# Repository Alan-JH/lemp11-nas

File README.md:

# lemp11-nas
Lemur Pro 11 to Low Power NAS Conversion

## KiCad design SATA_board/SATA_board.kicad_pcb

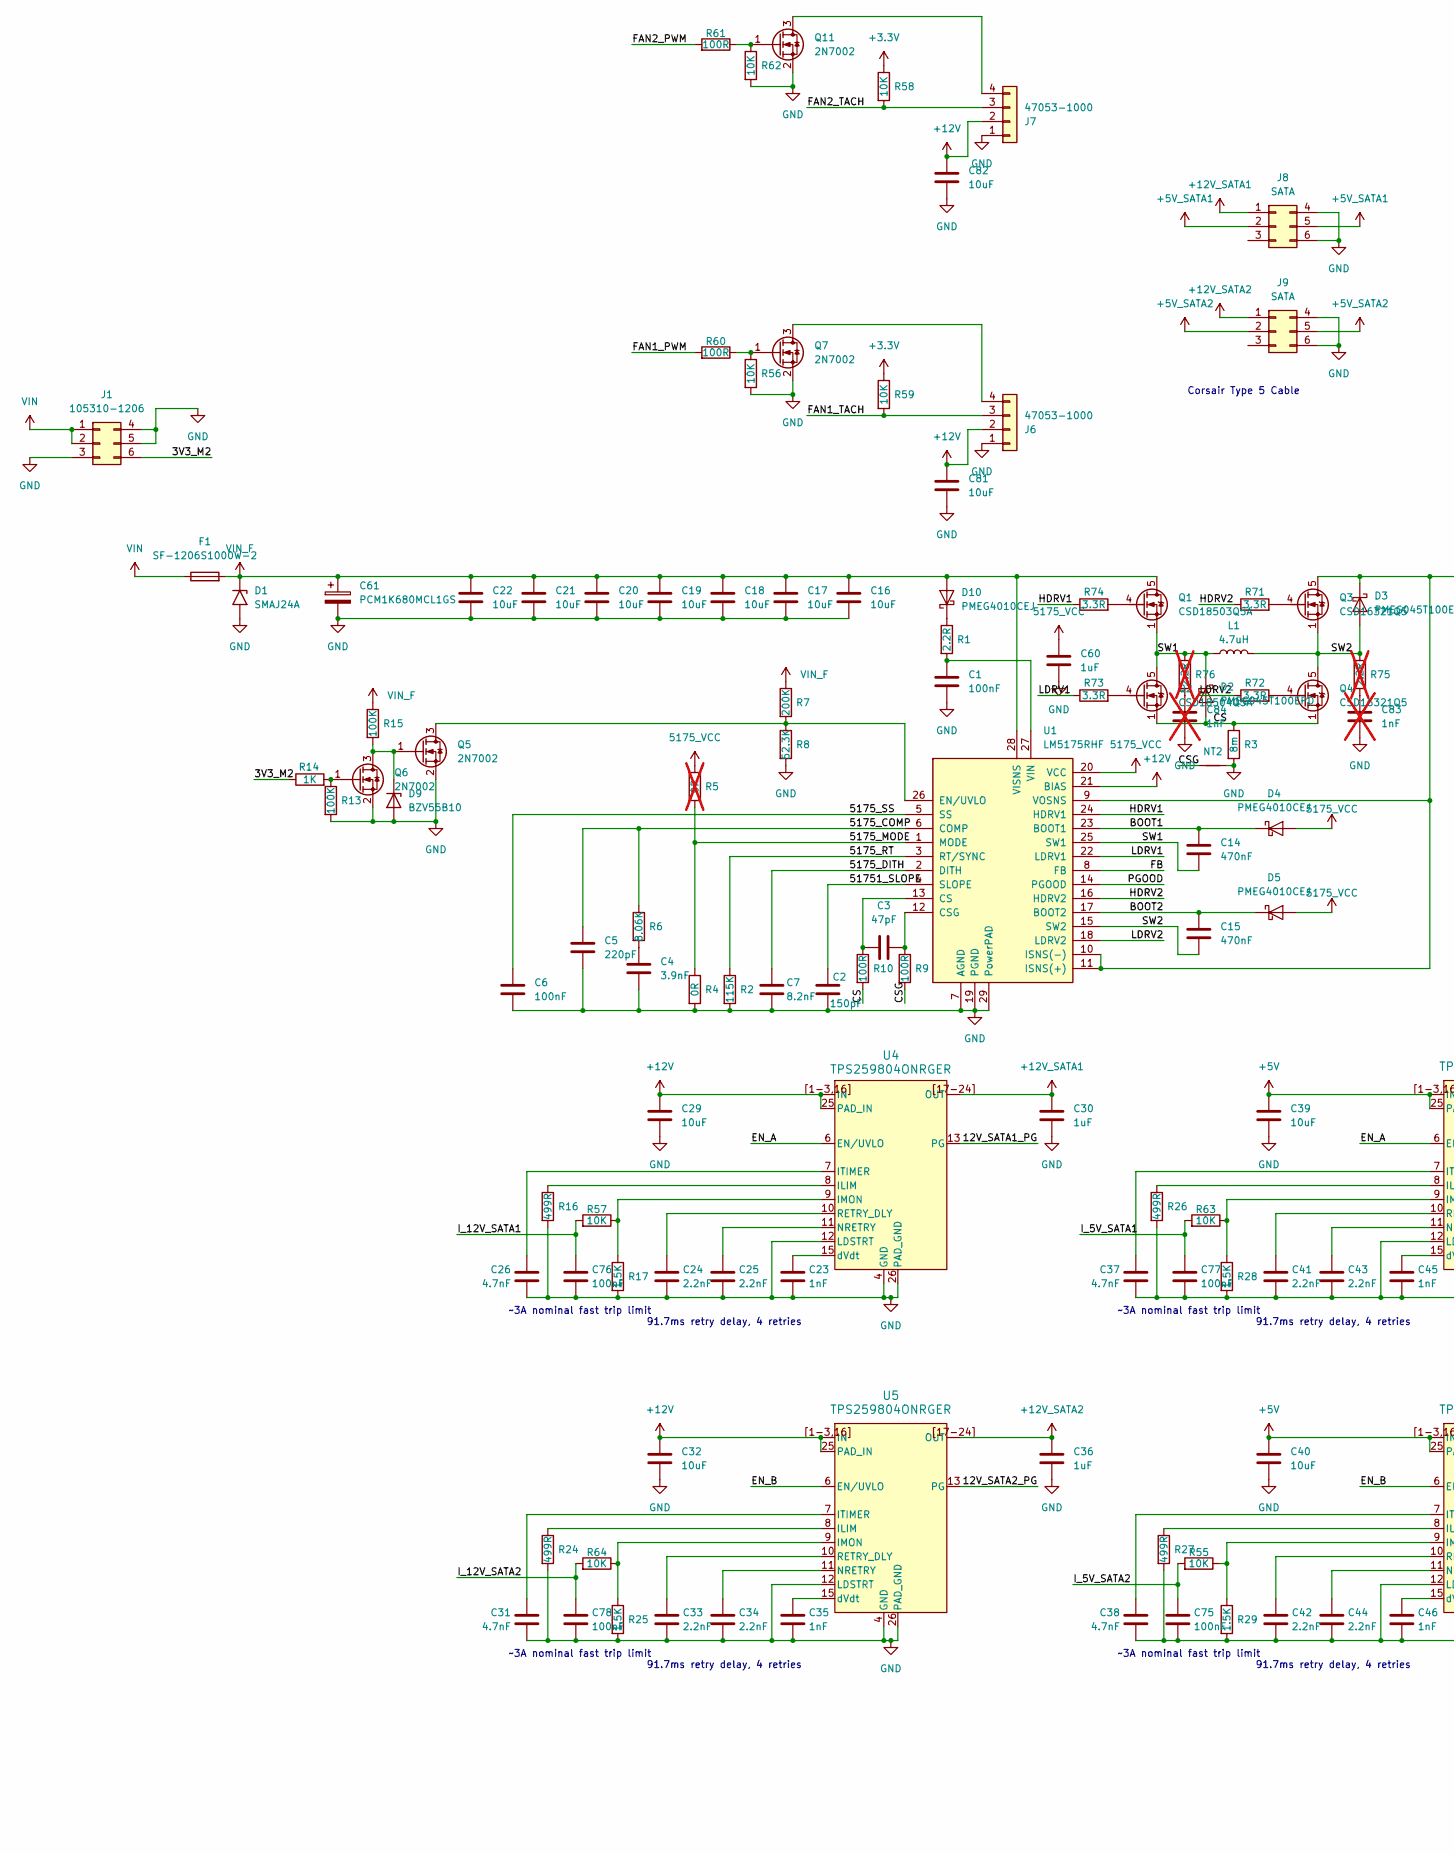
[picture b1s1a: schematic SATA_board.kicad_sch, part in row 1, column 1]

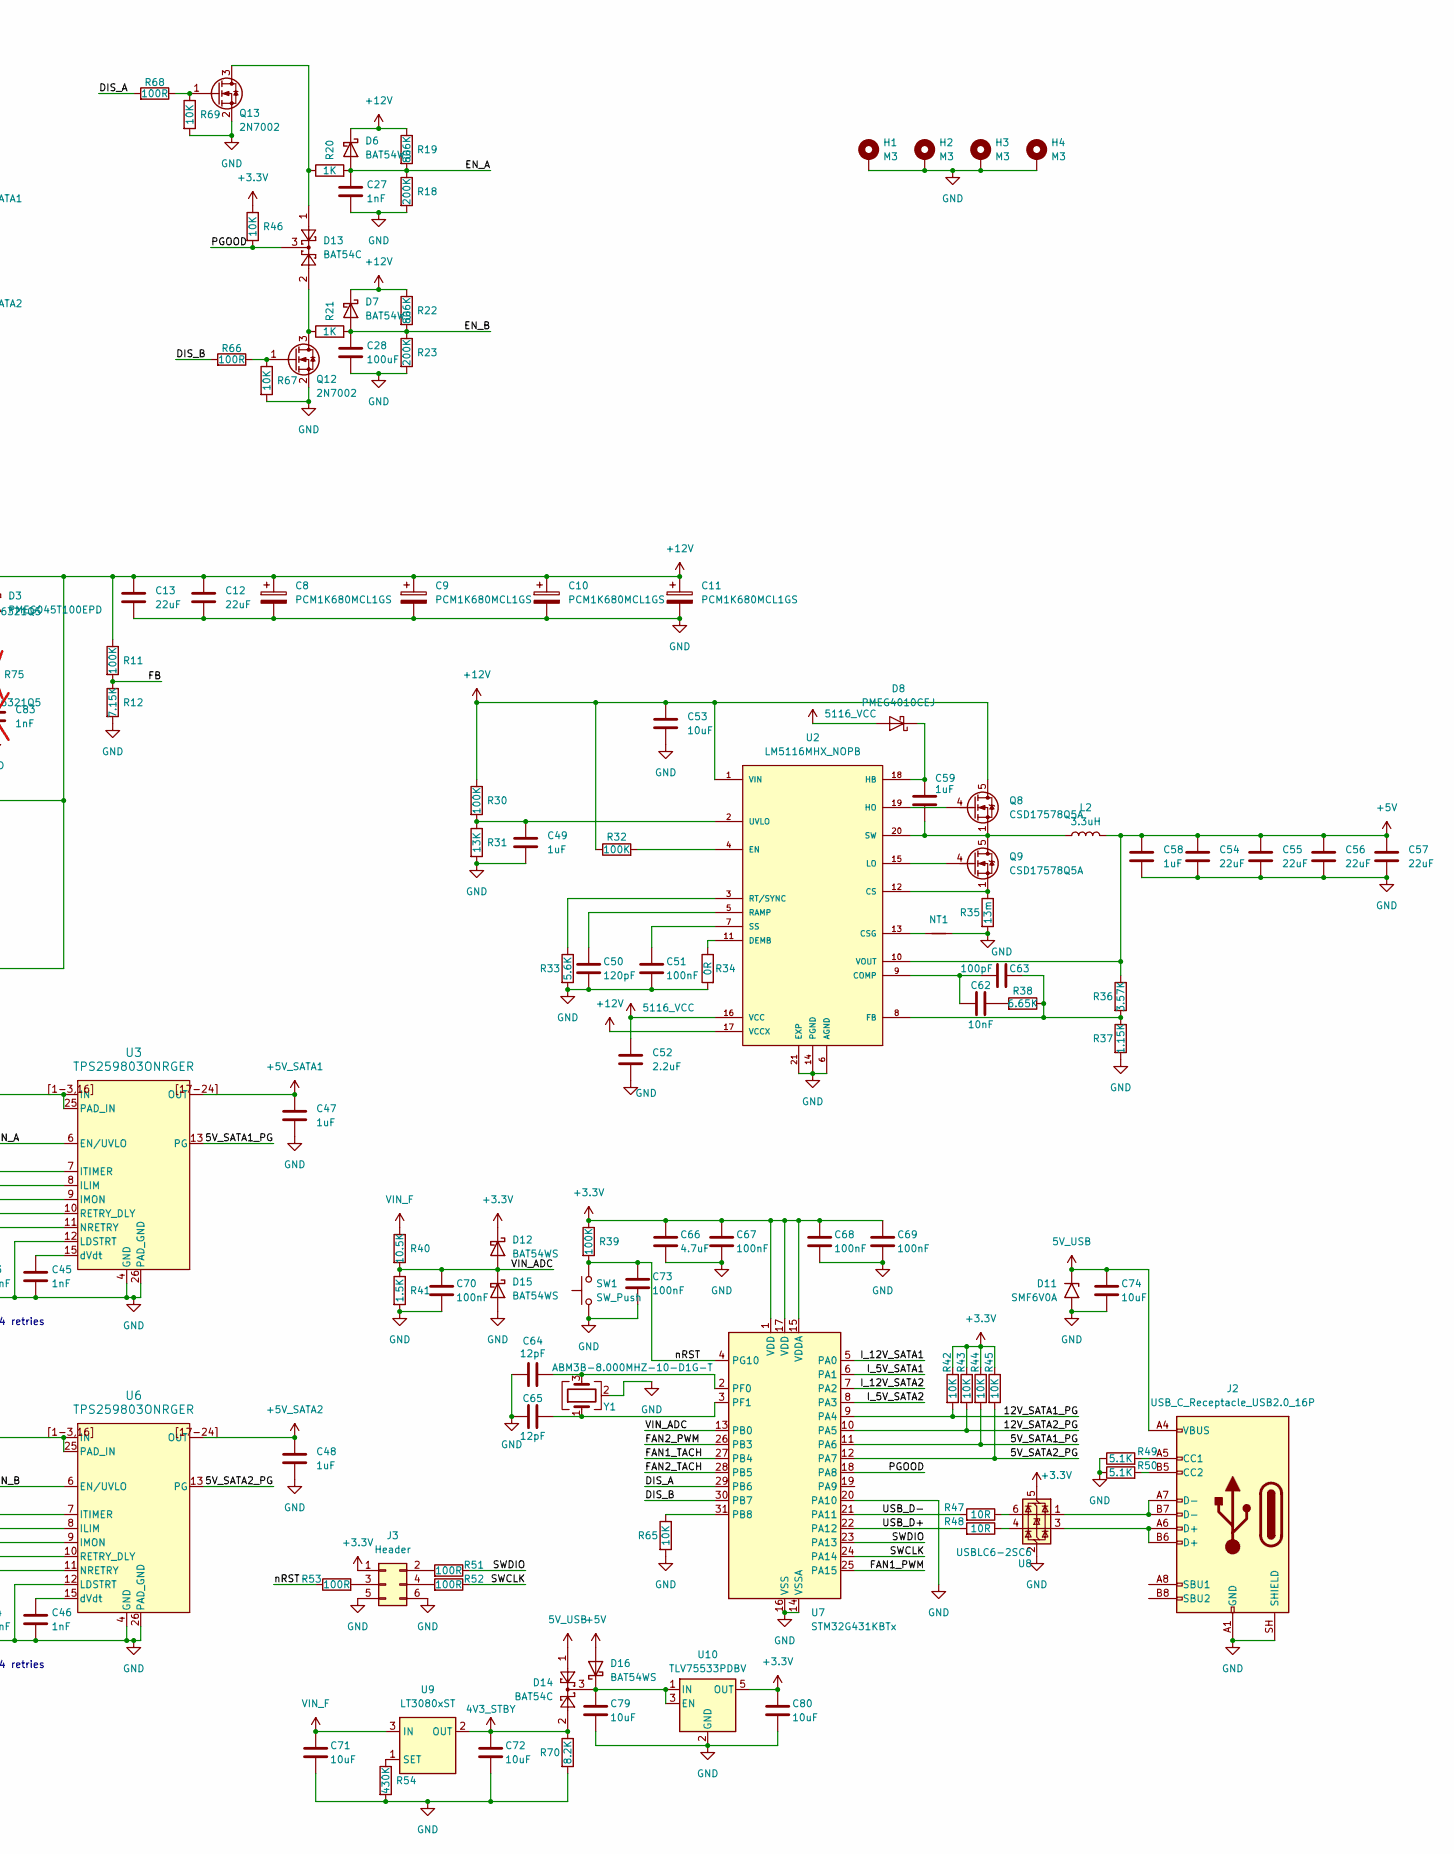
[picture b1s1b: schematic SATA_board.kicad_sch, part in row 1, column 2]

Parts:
C1, C51, C67, C68, C69, C70, C73, C75, C76, C77, C78: 100nF; C_0603_1608Metric
C2: 150pF; C_0402_1005Metric
C3: 47pF; C_0402_1005Metric
C4: 3.9nF; C_0402_1005Metric
C5: 220pF; C_0402_1005Metric
C6: 100nF; C_0402_1005Metric
C7: 8.2nF; C_0402_1005Metric
C8, C9, C10, C11, C61: PCM1K680MCL1GS; CP_Elec_10x10
C12, C13, C54, C55, C56, C57: 22uF; C_1210_3225Metric
C14, C15: 470nF; C_0603_1608Metric
C16, C17, C18, C19, C20, C21, C22, C53, C71: 10uF; C_1210_3225Metric
C23, C27, C35, C45, C46: 1nF; C_0603_1608Metric
C24, C25, C33, C34, C41, C42, C43, C44: 2.2nF; C_0603_1608Metric
C26, C31, C37, C38: 4.7nF; C_0603_1608Metric
C28: 100uF; C_1210_3225Metric
C29, C32, C39, C40, C72, C74, C79, C80, C81, C82: 10uF; C_0805_2012Metric
C30, C36, C47, C48, C49, C58, C59, C60: 1uF; C_0603_1608Metric
C50: 120pF; C_0603_1608Metric
C52: 2.2uF; C_0603_1608Metric
C62: 10nF; C_0603_1608Metric
C63: 100pF; C_0603_1608Metric
C64, C65: 12pF; C_0402_1005Metric
C66: 4.7uF; C_0603_1608Metric
C83, C84: 1nF; C_0805_2012Metric; not fitted
D1: SMAJ24A; D_SMA
D2, D3: PMEG045T100EPD; Nexperia_CFP15_SOT-1289
D4, D5, D8, D10: PMEG4010CEJ; D_SOD-323F
D6, D7, D12, D15, D16: BAT54WS; D_SOD-323F
D9: BZV55B10; D_MiniMELF
D11: SMF6V0A; D_SMF
D13, D14: BAT54C; SOT-23
F1: SF-1206S1000W-2; Fuse_1206_3216Metric
H1, H2, H3, H4: M3; MountingHole_3.2mm_M3_DIN965_Pad
J1: 105310-1206; Molex_Nano-Fit_105310-xx06_2x03_P2.50mm_Vertical
J2: USB_C_Receptacle_USB2.0_16P; USB_C_Receptacle_GCT_USB4105-xx-A_16P_TopMnt_Horizontal
J3: Header; PinHeader_2x03_P2.54mm_Vertical
J6, J7: 47053-1000; FanPinHeader_1x04_P2.54mm_Vertical
J8, J9: SATA; Molex_Micro-Fit_3.0_43045-0612_2x03_P3.00mm_Vertical
L1: 4.7uH; L_Vishay_IHLP-6767
L2: 3.3uH; L_Vishay_IHLP-4040
NT1, NT2: NetTie-2_SMD_Pad0.5mm
Q1: CSD18503Q5A; TDSON-8-1
Q2: CSD18504Q5A; TDSON-8-1
Q3, Q4: CSD16321Q5; TDSON-8-1
Q5, Q6, Q7, Q11, Q12, Q13: 2N7002; SOT-23
Q8, Q9: CSD17578Q5A; TDSON-8-1
R1: 2.2R; R_0603_1608Metric
R2: 115K; R_0402_1005Metric
R3: 8m; R_2512_6332Metric
R4: 0R; R_0402_1005Metric
R5: 0R; R_0402_1005Metric; not fitted
R6: 8.06K; R_0402_1005Metric
R7, R18, R23: 200K; R_0603_1608Metric
R8: 52.3K; R_0603_1608Metric
R9, R10: 100R; R_0402_1005Metric
R11, R13, R15, R30, R32, R39: 100K; R_0603_1608Metric
R12: 7.15K; R_0603_1608Metric
R14, R20, R21: 1K; R_0603_1608Metric
R16, R24, R26, R27: 499R; R_0603_1608Metric
R17, R25, R28, R29, R41: 1.5K; R_0603_1608Metric
R19, R22: 806K; R_0603_1608Metric
R31: 13K; R_0603_1608Metric
R33: 5.6K; R_0603_1608Metric
R34: 0R; R_0603_1608Metric
R35: 13m; R_2512_6332Metric
R36: 3.57K; R_0603_1608Metric
R37: 1.15K; R_0603_1608Metric
R38: 6.65K; R_0603_1608Metric
R40: 10.5K; R_0603_1608Metric
R42, R43, R44, R45, R46, R55, R56, R57, R58, R59, R62, R63, R64, R65, R67, R69: 10K; R_0603_1608Metric
R47, R48: 10R; R_0402_1005Metric
R49, R50: 5.1K; R_0402_1005Metric
R51, R52, R53, R60, R61, R66, R68: 100R; R_0603_1608Metric
R54: 430K; R_0603_1608Metric
R70: 8.2K; R_0603_1608Metric
R71, R72, R73, R74: 3.3R; R_0402_1005Metric
R75, R76: 2.2R; R_0805_2012Metric; not fitted
SW1: SW_Push; SW_PUSH_6mm
U1: LM5175RHF; VQFN-28-1EP_4x5mm_P0.5mm_EP2.55x3.55mm
U2: LM5116MHX_NOPB; SOP65P640X110-21N; PARTREV H
U3, U6: TPS259803ONRGER; IC24_TPS259802ONRGER_TEX
U4, U5: TPS259804ONRGER; IC24_TPS259802ONRGER_TEX
U7: STM32G431KBTx; LQFP-32_7x7mm_P0.8mm
U8: USBLC6-2SC6; SOT-23-6
U9: LT3080xST; SOT-223
U10: TLV75533PDBV; SOT-23-5
Y1: ABM3B-8.000MHZ-10-D1G-T; Crystal_SMD_Abracon_ABM3B-4Pin_5.0x3.2mm

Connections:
4V3_STBY: C72.1, D14.2, R70.1, U9.2 (OUT), U9.4 (OUT)
5V_USB: C74.1, D11.1 (A1), D14.1, J2.A4 (VBUS), J2.A9 (VBUS), J2.B4 (VBUS), J2.B9 (VBUS)
5116_VCC: C52.1, D8.2 (A), U2.16 (VCC)
5175_VCC: C60.1, D4.2 (A), D5.2 (A), R5.1, U1.20 (VCC)
+3.3V: C66.1, C67.1, C68.1, C69.1, C80.1, D12.1 (K), J3.1, R39.1, R42.1, R43.1, R44.1, R45.1, R46.1, R58.1, R59.1, U7.1 (VDD), U7.15 (VDDA), U7.17 (VDD), U8.5 (VBUS), U10.5 (OUT)
+5V: C39.1, C40.1, C54.1, C55.1, C56.1, C57.1, C58.1, D16.2 (A), L2.2, R36.1, U2.10 (VOUT), U3.1 (IN), U3.2 (IN), U3.3 (IN), U3.16 (IN), U3.25 (PAD_IN), U3.[1-3,16] (IN), U6.1 (IN), U6.2 (IN), U6.3 (IN), U6.16 (IN), U6.25 (PAD_IN), U6.[1-3,16] (IN)
+5V_SATA1: C47.1, J8.2, J8.5, U3.17 (OUT), U3.18 (OUT), U3.19 (OUT), U3.20 (OUT), U3.21 (OUT), U3.22 (OUT), U3.23 (OUT), U3.24 (OUT), U3.[17-24] (OUT)
+5V_SATA2: C48.1, J9.2, J9.5, U6.17 (OUT), U6.18 (OUT), U6.19 (OUT), U6.20 (OUT), U6.21 (OUT), U6.22 (OUT), U6.23 (OUT), U6.24 (OUT), U6.[17-24] (OUT)
+12V: C8.1, C9.1, C10.1, C11.1, C12.1, C13.1, C29.1, C32.1, C53.1, C81.1, C82.1, D3.3 (K), D6.1 (K), D7.1 (K), J6.2, J7.2, Q3.5 (D), Q8.5 (D), R11.1, R19.1, R22.1, R30.1, R32.1, U1.9 (VOSNS), U1.10 (ISNS(-)), U1.11 (ISNS(+)), U1.21 (BIAS), U2.1 (VIN), U2.17 (VCCX), U4.1 (IN), U4.2 (IN), U4.3 (IN), U4.16 (IN), U4.25 (PAD_IN), U4.[1-3,16] (IN), U5.1 (IN), U5.2 (IN), U5.3 (IN), U5.16 (IN), U5.25 (PAD_IN), U5.[1-3,16] (IN)
+12V_SATA1: C30.1, J8.1, U4.17 (OUT), U4.18 (OUT), U4.19 (OUT), U4.20 (OUT), U4.21 (OUT), U4.22 (OUT), U4.23 (OUT), U4.24 (OUT), U4.[17-24] (OUT)
+12V_SATA2: C36.1, J9.1, U5.17 (OUT), U5.18 (OUT), U5.19 (OUT), U5.20 (OUT), U5.21 (OUT), U5.22 (OUT), U5.23 (OUT), U5.24 (OUT), U5.[17-24] (OUT)
/3V3_M2: J1.6, R14.1
/5V_SATA1_PG: R44.2, U3.13 (PG), U7.11 (PA6)
/5V_SATA2_PG: R45.2, U6.13 (PG), U7.12 (PA7)
/12V_SATA1_PG: R42.2, U4.13 (PG), U7.9 (PA4)
/12V_SATA2_PG: R43.2, U5.13 (PG), U7.10 (PA5)
/5175_COMP: C5.1, R6.1, U1.6 (COMP)
/5175_DITH: C7.1, U1.2 (DITH)
/5175_MODE: R4.1, R5.2, U1.1 (MODE)
/5175_RT: R2.1, U1.3 (RT/SYNC)
/5175_SS: C6.1, U1.5 (SS)
/51751_SLOPE: C2.1, U1.4 (SLOPE)
/BOOT1: C14.1, D4.1 (K), U1.23 (BOOT1)
/BOOT2: C15.1, D5.1 (K), U1.17 (BOOT2)
/CS: D2.1 (A), D2.2 (A), Q2.1 (S), Q2.2 (S), Q2.3 (S), Q4.1 (S), Q4.2 (S), Q4.3 (S), R3.1, R10.2
/CSG: NT2.1, R9.2
/DIS_A: R68.2, U7.29 (PB6)
/DIS_B: R66.2, U7.30 (PB7)
/EN_A: C27.1, D6.2 (A), R18.1, R19.2, R20.2, U3.6 (EN/UVLO), U4.6 (EN/UVLO)
/EN_B: C28.1, D7.2 (A), R21.2, R22.2, R23.1, U5.6 (EN/UVLO), U6.6 (EN/UVLO)
/FAN1_PWM: R60.2, U7.25 (PA15)
/FAN1_TACH: J6.3, R59.2, U7.27 (PB4)
/FAN2_PWM: R61.2, U7.26 (PB3)
/FAN2_TACH: J7.3, R58.2, U7.28 (PB5)
/FB: R11.2, R12.1, U1.8 (FB)
/HDRV1: R74.1, U1.24 (HDRV1)
/HDRV2: R71.1, U1.16 (HDRV2)
/I_5V_SATA1: C77.1, R63.2, U7.6 (PA1)
/I_5V_SATA2: C75.1, R55.2, U7.8 (PA3)
/I_12V_SATA1: C76.1, R57.2, U7.5 (PA0)
/I_12V_SATA2: C78.1, R64.2, U7.7 (PA2)
/LDRV1: R73.1, U1.22 (LDRV1)
/LDRV2: R72.1, U1.18 (LDRV2)
/PGOOD: D13.3, R46.2, U1.14 (PGOOD), U7.18 (PA8)
/SW1: C14.2, D2.3 (K), L1.1, Q1.1 (S), Q1.2 (S), Q1.3 (S), Q2.5 (D), R76.1, U1.25 (SW1)
/SW2: C15.2, D3.1 (A), D3.2 (A), L1.2, Q3.1 (S), Q3.2 (S), Q3.3 (S), Q4.5 (D), R75.1, U1.15 (SW2)
/SWCLK: R52.1, U7.24 (PA14)
/SWDIO: R51.1, U7.23 (PA13)
/USB_D+: R48.2, U7.22 (PA12)
/USB_D-: R47.2, U7.21 (PA11)
/VIN_ADC: C70.1, D12.2 (A), D15.1 (K), R40.2, R41.1, U7.13 (PB0)
/nRST: C73.1, R39.2, R53.1, SW1.2, U7.4 (PG10)
GND: C1.2, C2.2, C4.2, C5.2, C6.2, C7.2, C8.2, C9.2, C10.2, C11.2, C12.2, C13.2, C16.2, C17.2, C18.2, C19.2, C20.2, C21.2, C22.2, C23.2, C24.2, C25.2, C26.2, C27.2, C28.2, C29.2, C30.2, C31.2, C32.2, C33.2, C34.2, C35.2, C36.2, C37.2, C38.2, C39.2, C40.2, C41.2, C42.2, C43.2, C44.2, C45.2, C46.2, C47.2, C48.2, C49.2, C50.2, C51.2, C52.2, C53.2, C54.2, C55.2, C56.2, C57.2, C58.2, C60.2, C61.2, C64.1, C65.1, C66.2, C67.2, C68.2, C69.2, C70.2, C71.2, C72.2, C73.2, C74.2, C75.2, C76.2, C77.2, C78.2, C79.2, C80.2, C81.2, C82.2, C83.2, C84.2, D1.2 (A2), D9.2 (A), D11.2 (A2), D15.2 (A), H1.1 (1_1), H2.1 (1_1), H3.1 (1_1), H4.1 (1_1), J1.3, J1.4, J1.5, J2.A1 (GND), J2.A12 (GND), J2.B1 (GND), J2.B12 (GND), J2.SH (SHIELD), J3.5, J3.6, J6.1, J7.1, J8.4, J8.6, J9.4, J9.6, NT1.2, NT2.2, Q5.2 (S), Q6.2 (S), Q7.2 (S), Q11.2 (S), Q12.2 (S), Q13.2 (S), R2.2, R3.2, R4.2, R8.2, R12.2, R13.2, R16.2, R17.2, R18.2, R23.2, R24.2, R25.2, R26.2, R27.2, R28.2, R29.2, R31.2, R33.2, R34.2, R35.2, R37.2, R41.2, R49.1, R50.1, R54.2, R56.2, R62.2, R65.2, R67.2, R69.2, R70.2, SW1.1, U1.7 (AGND), U1.19 (PGND), U1.29 (PowerPAD), U2.6 (AGND), U2.14 (PGND), U2.21 (EXP), U3.4 (GND), U3.5 (GND), U3.12 (LDSTRT), U3.14 (GND), U3.26 (PAD_GND), U4.4 (GND), U4.5 (GND), U4.12 (LDSTRT), U4.14 (GND), U4.26 (PAD_GND), U5.4 (GND), U5.5 (GND), U5.12 (LDSTRT), U5.14 (GND), U5.26 (PAD_GND), U6.4 (GND), U6.5 (GND), U6.12 (LDSTRT), U6.14 (GND), U6.26 (PAD_GND), U7.14 (VSSA), U7.16 (VSS), U7.20 (PA10), U7.32 (VSS), U8.2 (GND), U10.2 (GND), Y1.2 (G), Y1.4 (G)
unnamed: C4.1, R6.2
unnamed: C62.1, R38.2
unnamed: C83.1, R75.2
unnamed: C84.1, R76.2
unnamed: C59.1, D8.1 (K), U2.18 (HB)
unnamed: D9.1 (K), Q5.1 (G), Q6.3 (D), R15.2
unnamed: D10.1 (K), R1.1
unnamed: C79.1, D14.3, D16.1 (K), U10.1 (IN), U10.3 (EN)
unnamed: J2.A5 (CC1), R49.2
unnamed: J2.B5 (CC2), R50.2
unnamed: J2.A6 (D+), J2.B6 (D+), U8.3 (I/O2)
unnamed: J2.A7 (D-), J2.B7 (D-), U8.1 (I/O1)
unnamed: J3.2, R51.2
unnamed: J3.3, R53.2
unnamed: J3.4, R52.2
unnamed: J6.4, Q7.3 (D)
unnamed: J7.4, Q11.3 (D)
unnamed: Q1.4 (G), R74.2
unnamed: Q2.4 (G), R73.2
unnamed: Q3.4 (G), R71.2
unnamed: Q4.4 (G), R72.2
unnamed: Q5.3 (D), R7.2, R8.1, U1.26 (EN/UVLO)
unnamed: Q6.1 (G), R13.1, R14.2
unnamed: Q7.1 (G), R56.1, R60.1
unnamed: Q8.4 (G), U2.19 (HO)
unnamed: C59.2, L2.1, Q8.1 (S), Q8.2 (S), Q8.3 (S), Q9.5 (D), U2.20 (SW)
unnamed: Q9.4 (G), U2.15 (LO)
unnamed: Q11.1 (G), R61.1, R62.1
unnamed: D13.2, Q12.3 (D), R21.1
unnamed: Q12.1 (G), R66.1, R67.1
unnamed: D13.1, Q13.3 (D), R20.1
unnamed: Q13.1 (G), R68.1, R69.1
unnamed: R47.1, U8.6 (I/O1)
unnamed: R48.1, U8.4 (I/O2)
unnamed: C3.1, R10.1, U1.13 (CS)
unnamed: C3.2, R9.1, U1.12 (CSG)
unnamed: C1.1, R1.2, U1.27 (VIN)
unnamed: C62.2, C63.1, U2.9 (COMP)
unnamed: Q9.1 (S), Q9.2 (S), Q9.3 (S), R35.1, U2.12 (CS)
unnamed: NT1.1, U2.13 (CSG)
unnamed: R34.1, U2.11 (DEMB)
unnamed: R32.2, U2.4 (EN)
unnamed: C63.2, R36.2, R37.1, R38.1, U2.8 (FB)
unnamed: C50.1, U2.5 (RAMP)
unnamed: R33.1, U2.3 (RT/SYNC)
unnamed: C51.1, U2.7 (SS)
unnamed: C49.1, R30.2, R31.1, U2.2 (UVLO)
unnamed: R26.1, U3.8 (ILIM)
unnamed: R28.1, R63.1, U3.9 (IMON)
unnamed: C37.1, U3.7 (ITIMER)
unnamed: C43.1, U3.11 (NRETRY)
unnamed: C41.1, U3.10 (RETRY_DLY)
unnamed: C45.1, U3.15 (dVdt)
unnamed: R16.1, U4.8 (ILIM)
unnamed: R17.1, R57.1, U4.9 (IMON)
unnamed: C26.1, U4.7 (ITIMER)
unnamed: C25.1, U4.11 (NRETRY)
unnamed: C24.1, U4.10 (RETRY_DLY)
unnamed: C23.1, U4.15 (dVdt)
unnamed: R24.1, U5.8 (ILIM)
unnamed: R25.1, R64.1, U5.9 (IMON)
unnamed: C31.1, U5.7 (ITIMER)
unnamed: C34.1, U5.11 (NRETRY)
unnamed: C33.1, U5.10 (RETRY_DLY)
unnamed: C35.1, U5.15 (dVdt)
unnamed: R27.1, U6.8 (ILIM)
unnamed: R29.1, R55.1, U6.9 (IMON)
unnamed: C38.1, U6.7 (ITIMER)
unnamed: C44.1, U6.11 (NRETRY)
unnamed: C42.1, U6.10 (RETRY_DLY)
unnamed: C46.1, U6.15 (dVdt)
unnamed: R65.1, U7.31 (PB8)
unnamed: C64.2, U7.2 (PF0), Y1.3
unnamed: C65.2, U7.3 (PF1), Y1.1
unnamed: R54.1, U9.1 (SET)
VIN: F1.1, J1.1, J1.2
VIN_F: C16.1, C17.1, C18.1, C19.1, C20.1, C21.1, C22.1, C61.1, C71.1, D1.1 (A1), D10.2 (A), F1.2, Q1.5 (D), R7.1, R15.1, R40.1, U1.28 (VISNS), U9.3 (IN)

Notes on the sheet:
~3A nominal fast trip limit
91.7ms retry delay, 4 retries
Corsair Type 5 Cable

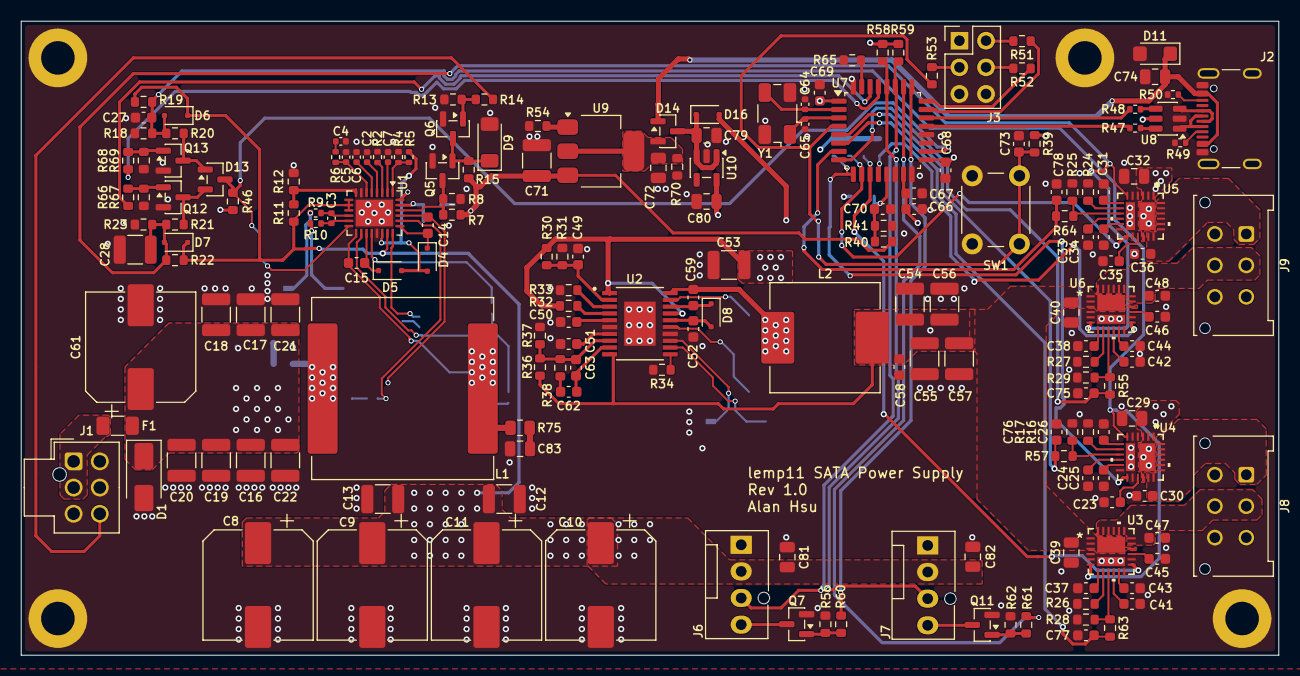
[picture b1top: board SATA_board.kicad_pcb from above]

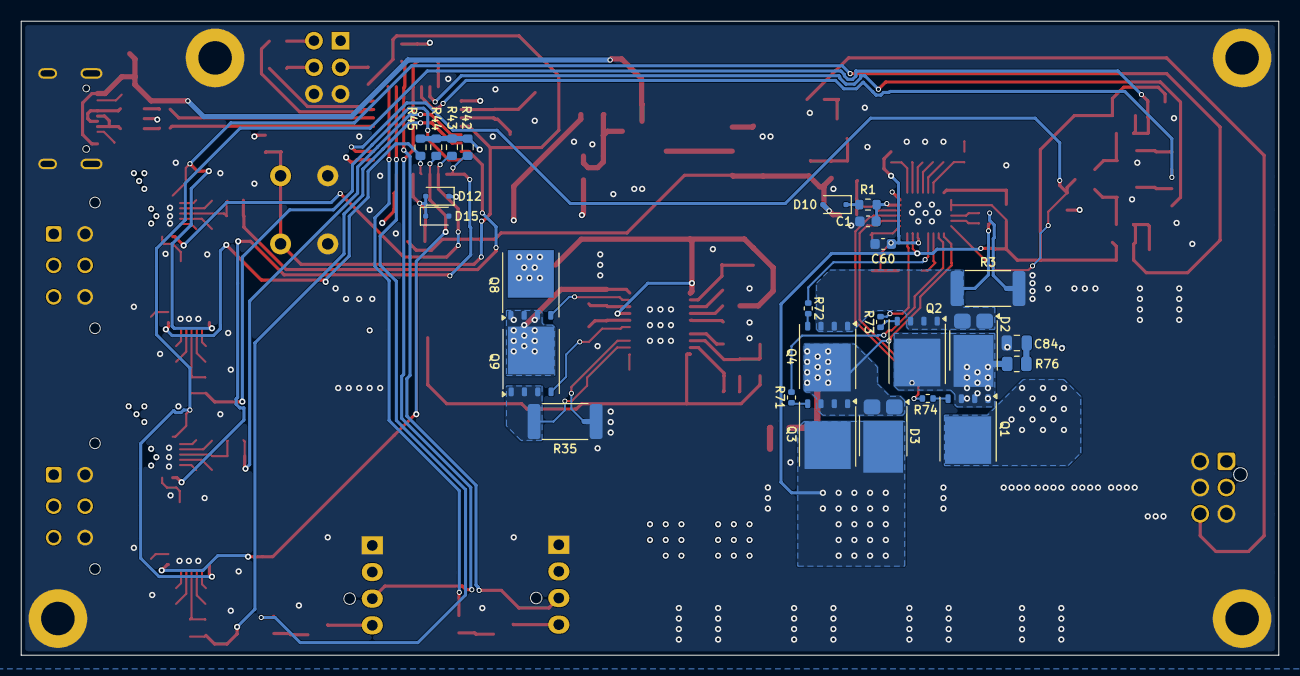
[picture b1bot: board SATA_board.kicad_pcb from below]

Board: 4 copper layers, 120.0 x 60.5 mm, 216 parts (28 on the bottom side), 130 nets.

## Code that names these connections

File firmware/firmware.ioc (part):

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Mcu.Name=STM32G431K(6-8-B)Tx
Mcu.Package=LQFP32
Mcu.UserName=STM32G431KBTx
PA0.Mode=IN1-Single-Ended
PA0.Signal=ADC1_IN1
PA1.Mode=IN2-Single-Ended
PA1.Signal=ADC1_IN2
PA11.Mode=Device
PA11.Signal=USB_DM
PA12.Mode=Device
PA12.Signal=USB_DP
PA13.Mode=Serial_Wire
PA13.Signal=SYS_JTMS-SWDIO
PA14.Mode=Serial_Wire
PA14.Signal=SYS_JTCK-SWCLK
PA15.Signal=S_TIM2_CH1
PA2.Mode=IN3-Single-Ended
PA2.Signal=ADC1_IN3
PA3.Mode=IN4-Single-Ended
PA3.Signal=ADC1_IN4
PA4.Signal=GPIO_Input
PA5.Signal=GPIO_Input
PA6.Signal=GPIO_Input
PA7.Signal=GPIO_Input
PA8.Signal=GPIO_Input
PB0.Mode=IN15-Single-Ended
PB0.Signal=ADC1_IN15
PB3.Signal=S_TIM2_CH2
PB4.Signal=GPXTI4
PB5.Signal=GPXTI5
PB6.Signal=GPIO_Output
PB7.Signal=GPIO_Output
PF0-OSC_IN.Mode=HSE-External-Oscillator
PF0-OSC_IN.Signal=RCC_OSC_IN
PF1-OSC_OUT.Mode=HSE-External-Oscillator
PF1-OSC_OUT.Signal=RCC_OSC_OUT
RCC.HSE_VALUE=8000000
RCC.SYSCLKFreq_VALUE=48000000
RCC.SYSCLKSource=RCC_SYSCLKSOURCE_PLLCLK
board=custom
